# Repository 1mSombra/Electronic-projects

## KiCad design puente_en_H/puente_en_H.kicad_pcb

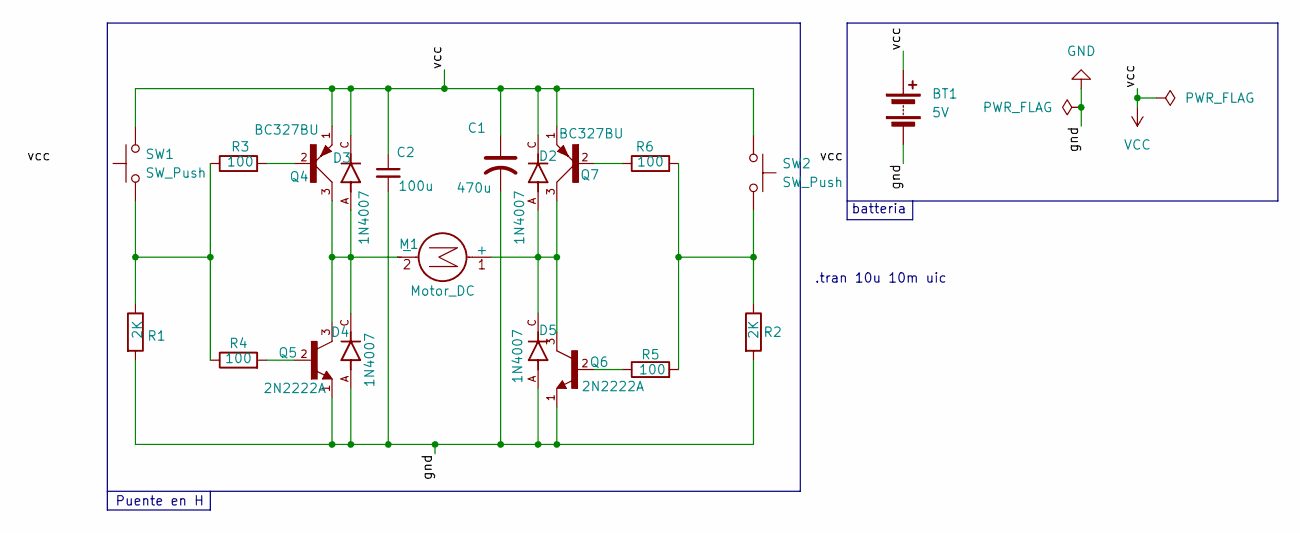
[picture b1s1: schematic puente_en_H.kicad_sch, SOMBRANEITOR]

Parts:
BT1: 5V; TerminalBlock_Phoenix_PT-1,5-2-5.0-H_1x02_P5.00mm_Horizontal
C1: 470u; Electrolitico
C2: 100u; lenteja
D2, D3, D4, D5: 1N4007; Diode1N4007; PARTREV G
M1: Motor_DC; TerminalBlock_Phoenix_PT-1,5-2-5.0-H_1x02_P5.00mm_Horizontal
Q4, Q7: BC327BU; BC32740BU
Q5, Q6: 2N2222A; 2n2222A; PARTREV N/A
R1, R2: 2K; R_Axial_DIN0207_L6.3mm_D2.5mm_P7.62mm_Horizontal
R3, R4, R5, R6: 100; R_Axial_DIN0207_L6.3mm_D2.5mm_P7.62mm_Horizontal
SW1, SW2: SW_Push; SW_PUSH_1P1T_6x3.5mm_H5.0_APEM_MJTP1250

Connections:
GND: BT1.2 (-), C1.2, C2.2, D4.A, D5.A, Q5.1, Q6.1, R1.2, R2.2
unnamed: D2.A, D5.C, M1.1 (+), Q6.3, Q7.3
unnamed: D3.A, D4.C, M1.2 (-), Q4.3, Q5.3
unnamed: Q4.2, R3.2
unnamed: Q5.2, R4.2
unnamed: Q6.2, R5.1
unnamed: Q7.2, R6.1
unnamed: R1.1, R3.1, R4.1, SW1.1
unnamed: R2.1, R5.2, R6.2, SW2.2
VCC: BT1.1 (+), C1.1, C2.1, D2.C, D3.C, Q4.1, Q7.1, SW1.2, SW2.1

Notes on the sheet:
Puente en H
.tran 10u 10m uic
batteria

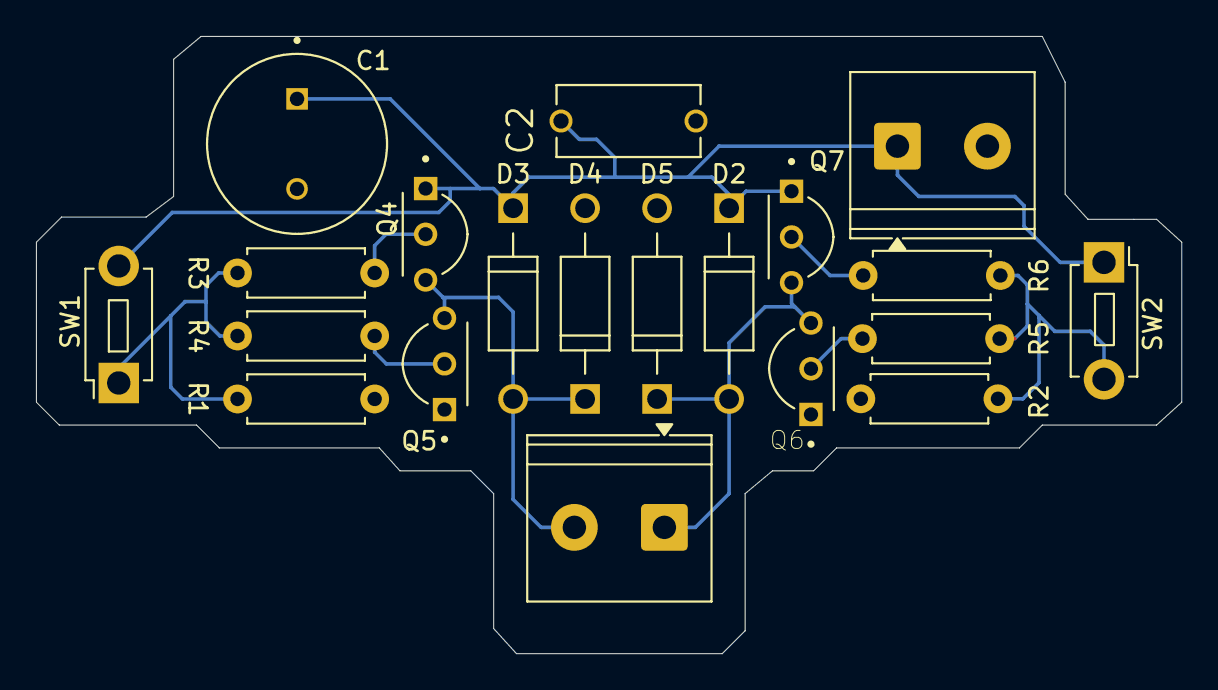
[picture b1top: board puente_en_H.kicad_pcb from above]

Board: 2 copper layers, 63.6 x 34.3 mm, 20 parts (0 on the bottom side), 10 nets.

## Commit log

2026-06-26 Primer commit: Mis proyectos de KiCad listos
2026-06-26 add simulator and models
